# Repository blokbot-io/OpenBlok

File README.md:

<div align="center">

# OpenBlok | blokbot.io

&nbsp;

&nbsp;

</div>

## Table of Contents

- [OpenBlok | blokbot.io](#openblok--blokbotio)
  - [Table of Contents](#table-of-contents)
  - [Hardware Requirements](#hardware-requirements)
  - [Installation](#installation)
  - [Directory Structure](#directory-structure)
  - [Community and Contributing](#community-and-contributing)

OpenBlok is an open source Lego identification and sorting system using AI models developed by [blokbot.io](https://blokbot.io)

The identification system requires a specific camera setup that can be purchased from [blokbot.io](https://blokbot.io) or can be created by referencing our technical guide.

## Hardware Requirements

There are several AI models that provide flexibility to the configuration of OpenBlok. Please refer to our standards guide for more information. Additionally, you may purchase the desktop dev kit for a quick start.

A camera stream is required to use OpenBlok, if no input device is found, OpenBlok will download a sample video stream to use as a test. The following cameras have been tested and are known to work:

- [MOKOSE 4K HD USB](https://www.amazon.com/gp/product/B08FHBRKSK/ref=ppx_yo_dt_b_search_asin_title?ie=UTF8&psc=1) with [Arducam 8-50mm C-Mount Zoom Lens](https://www.amazon.com/gp/product/B08PYMBX9T/ref=ppx_yo_dt_b_search_asin_title?ie=UTF8&psc=1)

To achieve higher frame rates, the use of a graphics card or other AI model accelerator can be used.

## Installation

OpenBlok has been developed and deigned to run on *Ubuntu 22.04 LTS. It is recommended to run `apt-get update` and `apt-get upgrade` before installing OpenBlok.

For custom installation options, please refer to the [installation guide](docs/installer.md). Otherwise, you can install OpenBlok using the following command:

```bash
sudo wget -qO- openblok.blokbot.io | bash /dev/stdin
```

**\* Only tested using desktop version, PR welcome for minimum GUI installation version.**

## Directory Structure

``` bash
.
├── docs                # Documentation
└── bloks               # System Functions
    ├── modules         # Modules
    └── utils           # Supporting Utilities
├── display             # Visualization
├── peripherals         # Peripherals
└── modeled             # AI model implementation
    └── models          # AI model files
```

## Community and Contributing

OpenBlock is developed by [Blok Bot](https://blokbot.io/) and by users like you. We welcome both pull requests and issues on [GitHub](https://github.com/blokbot-io/OpenBlok). Bug fixes and new features are encouraged.

<div align="center">

</div>

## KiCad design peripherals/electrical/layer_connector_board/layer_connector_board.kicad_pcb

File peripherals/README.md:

## Hardware

To control the steppers a [BIQU A4988](https://www.amazon.com/gp/product/B01FFFYVV8/ref=ppx_yo_dt_b_search_asin_title?ie=UTF8&psc=1) driver is used. [See Example](https://www.makerguides.com/a4988-stepper-motor-driver-arduino-tutorial/).

For homing and positioning an optical switch is used, connected to pin 8 of the Arduino.

## Installation

The [AccelStepper library](https://www.airspayce.com/mikem/arduino/AccelStepper/classAccelStepper.html#a96685e0945b7cf75d5959da679cd911e) is required.

## Feeding Stages

[Break Beam](https://www.adafruit.com/product/2167)
[Break Bean - Arduino Example](https://learn.adafruit.com/ir-breakbeam-sensors/arduino)

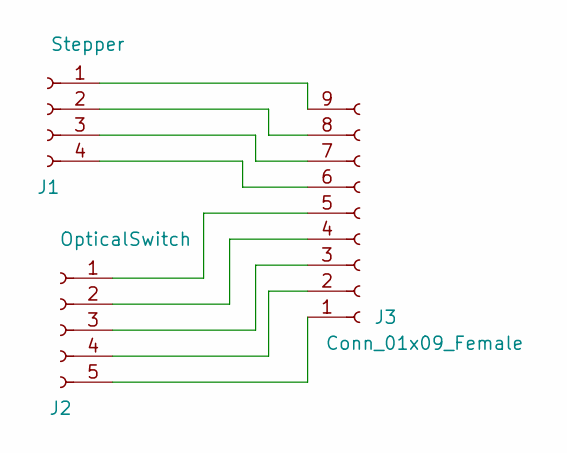
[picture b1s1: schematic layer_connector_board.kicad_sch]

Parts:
J1: Stepper; JST_XH_B4B-XH-A_1x04_P2.50mm_Vertical
J2: OpticalSwitch; JST_XH_B5B-XH-A_1x05_P2.50mm_Vertical
J3: Conn_01x09_Female; PhoenixContact_MSTBA_2,5_9-G_1x09_P5.00mm_Horizontal

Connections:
unnamed: J1.1, J3.9
unnamed: J1.2, J3.8
unnamed: J1.3, J3.7
unnamed: J1.4, J3.6
unnamed: J2.1, J3.5
unnamed: J2.2, J3.4
unnamed: J2.3, J3.3
unnamed: J2.4, J3.2
unnamed: J2.5, J3.1

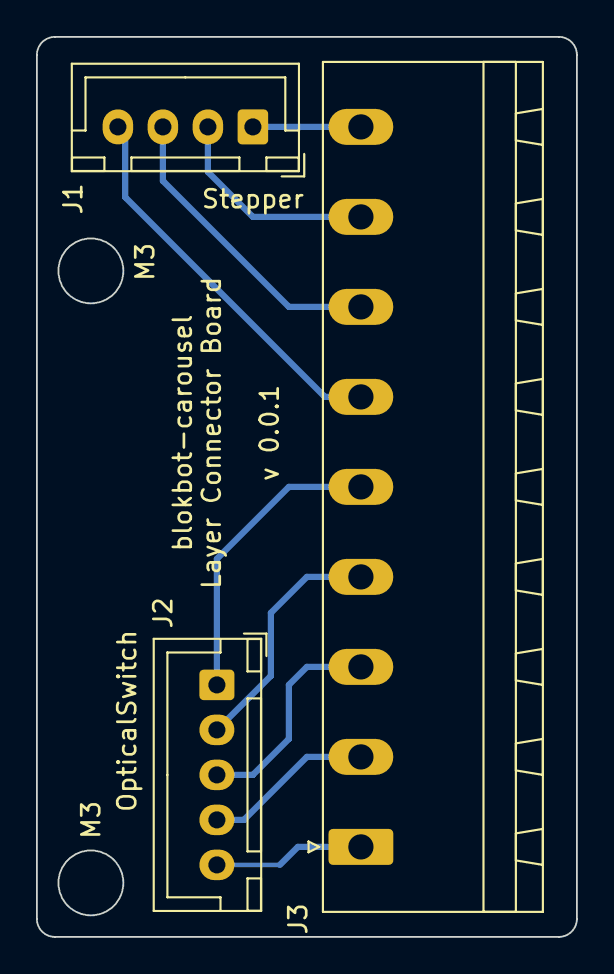
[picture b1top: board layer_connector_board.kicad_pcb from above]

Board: 2 copper layers, 30.0 x 50.0 mm, 3 parts (0 on the bottom side), 9 nets.

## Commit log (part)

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2022-09-08 add time checks
2022-09-08 add a queue
2022-09-08 added queu
2022-09-08 added crop
2022-09-09 rotate image
2022-09-09 added e2e model
2022-09-09 reduce buffer
2022-09-09 change buffer
2022-09-10 Added arduino code
2022-09-10 moved code
2022-09-12 Added Arduino
2022-09-13 added serial controller
2022-09-13 started serial thread
2022-09-13 less gusesses
2022-09-13 change confidence
2022-09-13 added serial lsitner
2022-09-13 stop capturing
2022-09-20 general linting
2022-09-20 added ci
2022-09-20 Bump tensorflow from 2.9 to 2.9.1
    Bumps [tensorflow](https://github.com/tensorflow/tensorflow) from 2.9 to 2.9.1.
    - [Release notes](https://github.com/tensorflow/tensorflow/releases)
    - [Changelog](https://github.com/tensorflow/tensorflow/blob/master/RELEASE.md)
    - [Commits](https://github.com/tensorflow/tensorflow/compare/v2.9.0...v2.9.1)
    ---
    updated-dependencies:
2022-09-20 linting
2022-09-29 Added Image Upload
2022-09-29 Added boto3 requirement
2022-09-29 Changed What Gets Uploaded
2022-09-29 changed location model
2022-11-03 Added a 2L
2022-11-03 Removed vs code
2022-11-11 Consolidated Carousel Repo
2022-11-19 Full 5L Working
    Made master/slave Arduino to get all 5 layers of the carousel working.
2022-11-20 Linting
    Linted and Added Discord server link
2022-11-20 Added an updater to get new models
    Added the weights for the location model
2022-11-21 Changed location model to a class
2022-11-21 Loading Model
    No compiling model
2022-11-21 Time Changes
2022-11-21 e2e Class
2022-11-21 Linted
2022-11-21 Bump tensorflow from 2.9.1 to 2.9.3
    Bumps [tensorflow](https://github.com/tensorflow/tensorflow) from 2.9.1 to 2.9.3.
    - [Release notes](https://github.com/tensorflow/tensorflow/releases)
    - [Changelog](https://github.com/tensorflow/tensorflow/blob/master/RELEASE.md)
    - [Commits](https://github.com/tensorflow/tensorflow/compare/v2.9.1...v2.9.3)
    ---
    updated-dependencies:
2022-11-21 Added STL files
2022-11-27 wip: adding installer
2022-11-27 Updated Python Version
2022-11-27 Improved Docs
2022-11-27 Expanded Installer
2022-11-27 wip: installer
2022-11-27 expanded docs
2022-11-27 Changed release
2022-11-28 Removed extra display
2022-11-28 readme updates
2022-11-29 Added FPS counter
2022-11-29 fix: installer permissions
2022-11-29 fix: stats
2022-11-29 increase buffer length
2022-11-29 Code cleanup
2023-02-07 added system info file and storage location info
2023-02-07 add ob_storage
2023-02-07 fix: image save
2023-02-07 requirements update
2023-02-07 store metadata
2023-02-07 fixed naming
2023-02-07 add redis support
2023-02-07 cleanup redis storage
2023-02-07 using DB to fetch next frame
2023-02-07 move frame rotation to a subprocess
2023-02-07 less saving to config
2023-02-07 added print from multiprocesses
2023-02-07 cleanup
2023-02-07 fix decimal
2023-02-08 multiprocessing roi
2023-02-08 using roi
2023-02-08 fixed metadata
2023-02-08 reduced multiprocesses
2023-02-08 removed prints
2023-02-08 multiple prediction subprocesses
2023-02-08 use_multiprocessing=False
2023-02-08 change multiprocessing type
2023-02-08 pulled out clear
2023-02-08 move frames
2023-02-08 moving annotations
2023-02-09 split annotations
2023-02-09 rename function
2023-02-09 json.loads
2023-02-09 metadata
2023-02-09 switch crop to object
2023-02-09 drop storing cropped frame
2023-02-10 new data structure
2023-02-10 fix annotations
2023-02-10 bounding box refrence
2023-02-11 change location prediction to object
2023-02-11 clean up camera
2023-02-11 added sleeps
2023-02-11 more realtime
2023-02-11 longer FPS
2023-02-11 revert FPS
2023-02-17 added validation and s3 upload
2023-02-20 Testing improved speed
2023-02-23 perspective warp
2023-02-24 Added data stream and finished ROI example
2023-02-24 Switch method for ROI Capturing
2023-02-24 change to touple
2023-02-24 use raw frame
2023-02-27 change codec
2023-02-27 subprocess ROI
2023-02-27 change codecc
2023-02-27 optimize
2023-02-27 cleanup camera save
2023-02-27 improve get frame
2023-02-27 reduce tf verbosity
2023-02-27 reduce images taken
2023-02-27 remove vebosity
2023-02-27 skip frames
2023-02-27 remove verbose attempt
2023-02-27 add time marking
2023-02-27 change display to a thread
2023-02-27 test error
2023-02-27 remove stale frames
2023-02-27 more leway
2023-02-27 less drops
2023-03-01 separate out the carousel peripheral
2023-03-25 Bump tensorflow from 2.11.0 to 2.11.1
    Bumps [tensorflow](https://github.com/tensorflow/tensorflow) from 2.11.0 to 2.11.1.
    - [Release notes](https://github.com/tensorflow/tensorflow/releases)
    - [Changelog](https://github.com/tensorflow/tensorflow/blob/master/RELEASE.md)
    - [Commits](https://github.com/tensorflow/tensorflow/compare/v2.11.0...v2.11.1)
    ---
    updated-dependencies:
2023-03-27 Bump redis from 4.4.2 to 4.5.3
    Bumps [redis](https://github.com/redis/redis-py) from 4.4.2 to 4.5.3.
    - [Release notes](https://github.com/redis/redis-py/releases)
    - [Changelog](https://github.com/redis/redis-py/blob/master/CHANGES)
    - [Commits](https://github.com/redis/redis-py/compare/v4.4.2...v4.5.3)
    ---
    updated-dependencies:
2023-03-31 Bump redis from 4.4.2 to 4.4.4
    Bumps [redis](https://github.com/redis/redis-py) from 4.4.2 to 4.4.4.
    - [Release notes](https://github.com/redis/redis-py/releases)
    - [Changelog](https://github.com/redis/redis-py/blob/master/CHANGES)
    - [Commits](https://github.com/redis/redis-py/compare/v4.4.2...v4.4.4)
    ---
    updated-dependencies:
